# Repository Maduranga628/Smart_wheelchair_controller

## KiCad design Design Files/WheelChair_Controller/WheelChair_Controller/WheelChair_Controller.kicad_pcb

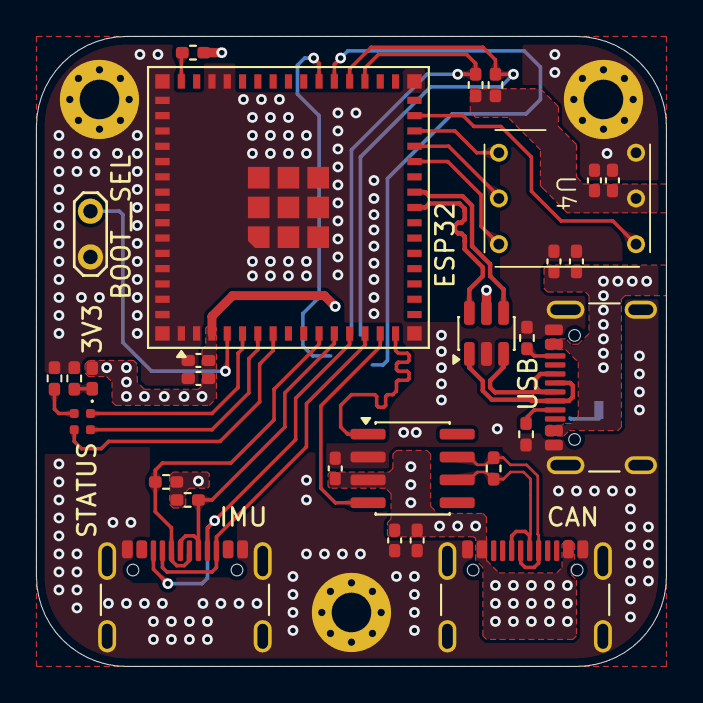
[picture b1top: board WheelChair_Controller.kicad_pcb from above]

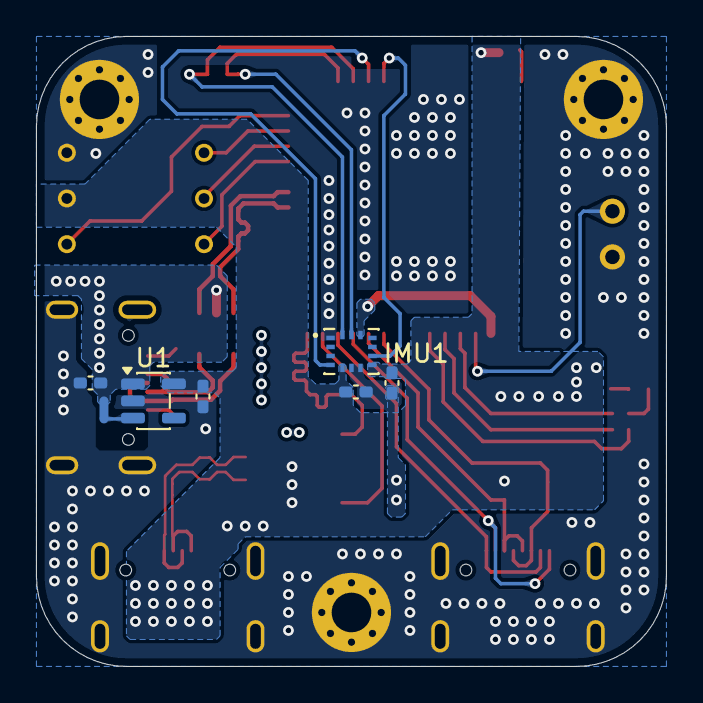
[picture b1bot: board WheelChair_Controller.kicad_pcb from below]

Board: 4 copper layers, 35.0 x 35.0 mm, 39 parts (7 on the bottom side), 33 nets.

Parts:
3V3: LED; LED_0402_1005Metric_Pad0.77x0.64mm_HandSolder
BOOT__SEL: Jumper_2_Open; TestPoint_2Pads_Pitch2.54mm_Drill0.8mm
C1, C2, C5, C6, C8, C10, C11, C12: 1u; C_0402_1005Metric_Pad0.74x0.62mm_HandSolder
C3, C4, C7, C9, C13: 100n; C_0402_1005Metric_Pad0.74x0.62mm_HandSolder
CAN: USB_C_Receptacle_USB2.0_16P; USB_C_Receptacle_GCT_USB4105-xx-A_16P_TopMnt_Horizontal
ESP32: ESP32-S3-MINI-1U; ESP32-S2-MINI-1U
IMU: USB_C_Receptacle_USB2.0_16P; USB_C_Receptacle_GCT_USB4105-xx-A_16P_TopMnt_Horizontal
IMU1: BMI270; XDCR_BMI270
MH1, MH2, MH3: MountingHole_Pad; MountingHole_2.2mm_M2_Pad_Via
NT1: NetTie_2; NetTie-2_SMD_Pad0.5mm
R1, R2: 330R; R_0402_1005Metric_Pad0.72x0.64mm_HandSolder
R3, R4, R5, R7, R8, R9, R10: 5k1; R_0402_1005Metric_Pad0.72x0.64mm_HandSolder
R6: 120R; R_0402_1005Metric_Pad0.72x0.64mm_HandSolder
STATUS: LED_RGB; LED_SK6812_EC15_1.5x1.5mm
U1: TLV75533PDBV; SOT-23-5
U2: USBLC6-2SC6; SOT-23-6
U3: SN65HVD232; SOIC-8_3.9x4.9mm_P1.27mm
U4: INMP441 Module; INMP441_Module
USB: USB_C_Receptacle_USB2.0_16P; USB_C_Receptacle_GCT_USB4105-xx-A_16P_TopMnt_Horizontal

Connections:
+3V3: 3V3.2 (A), C3.1, C4.1, C6.1, C7.1, C8.1, C9.1, C10.1, C11.1, C12.1, C13.1, CAN.A4 (VBUS), CAN.A9 (VBUS), CAN.B4 (VBUS), CAN.B9 (VBUS), ESP32.3 (3V3), IMU1.5 (VDDIO), IMU1.8 (VDD), IMU1.12 (CSB), R5.1, R7.1, R8.1, R9.1, R10.1, U1.5 (OUT), U3.3 (VCC), U4.5 (VDD)
+VBUS: C1.1, C2.1, C5.1, NT1.1, U1.1 (IN), U2.5 (VBUS), USB.A4 (VBUS), USB.A9 (VBUS), USB.B4 (VBUS), USB.B9 (VBUS)
/BOOT_SEL: BOOT__SEL.2 (B), ESP32.4 (IO0)
/CAN+: CAN.A6 (D+), CAN.B6 (D+), R6.2, U3.7 (CANH)
/CAN-: CAN.A7 (D-), CAN.B7 (D-), R6.1, U3.6 (CANL)
/CAN_RX: ESP32.14 (IO10), U3.4 (R)
/CAN_TX: ESP32.15 (IO11), U3.1 (D)
/EN: ESP32.45 (EN), R5.2
/I2S_L/R: ESP32.28 (IO33), U4.1 (L/R)
/I2S_SCL: ESP32.26 (IO26), U4.3 (SCK)
/I2S_SD: ESP32.29 (IO34), U4.4 (SD)
/I2S_WS: ESP32.27 (IO47), U4.2 (WS)
/IMU1_INT1: ESP32.35 (IO39), IMU1.4 (INT1)
/IMU1_INT2: ESP32.36 (IO40), IMU1.9 (INT2)
/IMU1_SCL: ESP32.33 (IO37), IMU1.13 (SCX), R9.2
/IMU1_SDA: ESP32.34 (IO38), IMU1.14 (SDX), R10.2
/IMU2_INT1: ESP32.13 (IO9), IMU.A5 (CC1), IMU.B5 (CC2)
/IMU2_INT2: ESP32.12 (IO8), IMU.A8 (SBU1), IMU.B8 (SBU2)
/IMU2_SCL: ESP32.10 (IO6), IMU.A7 (D-), IMU.B7 (D-), R8.2
/IMU2_SDA: ESP32.11 (IO7), IMU.A6 (D+), IMU.B6 (D+), R7.2
/LDO_EN: NT1.2, U1.3 (EN)
/PWR_RDY: 3V3.1 (K), R1.1
/STATUS: R2.2, STATUS.4 (K)
/STATUS_LED1: ESP32.6 (IO2), STATUS.2 (RA)
/STATUS_LED2: ESP32.5 (IO1), STATUS.3 (GA)
/STATUS_LED3: ESP32.7 (IO3), STATUS.1 (BA)
/USBD+: U2.3 (I/O2), USB.A6 (D+), USB.B6 (D+)
/USBD-: U2.1 (I/O1), USB.A7 (D-), USB.B7 (D-)
/USB_CC1: R4.1, USB.A5 (CC1)
/USB_CC2: R3.1, USB.B5 (CC2)
/USB_D+: ESP32.24 (USB_D+), U2.4 (I/O2)
/USB_D-: ESP32.23 (USB_D-), U2.6 (I/O1)
GND: BOOT__SEL.1 (A), C1.2, C2.2, C3.2, C4.2, C5.2, C6.2, C7.2, C8.2, C9.2, C10.2, C11.2, C12.2, C13.2, CAN.A1 (GND), CAN.A12 (GND), CAN.B1 (GND), CAN.B12 (GND), CAN.S1 (SHIELD), ESP32.1 (GND), ESP32.2 (GND), ESP32.42 (GND), ESP32.43 (GND), ESP32.46 (GND), ESP32.47 (GND), ESP32.48 (GND), ESP32.49 (GND), ESP32.50 (GND), ESP32.51 (GND), ESP32.52 (GND), ESP32.53 (GND), ESP32.54 (GND), ESP32.55 (GND), ESP32.56 (GND), ESP32.57 (GND), ESP32.58 (GND), ESP32.59 (GND), ESP32.60 (GND), ESP32.61 (GND), ESP32.62 (GND), ESP32.63 (GND), ESP32.64 (GND), ESP32.65 (GND), IMU.A1 (GND), IMU.A12 (GND), IMU.B1 (GND), IMU.B12 (GND), IMU.S1 (SHIELD), IMU1.1 (SDO), IMU1.6 (GNDIO), IMU1.7 (GND), MH1.1, MH2.1, MH3.1, R1.2, R2.1, R3.2, R4.2, U1.2 (GND), U2.2 (GND), U3.2 (GND), U4.6 (GND), USB.A1 (GND), USB.A12 (GND), USB.B1 (GND), USB.B12 (GND), USB.S1 (SHIELD)

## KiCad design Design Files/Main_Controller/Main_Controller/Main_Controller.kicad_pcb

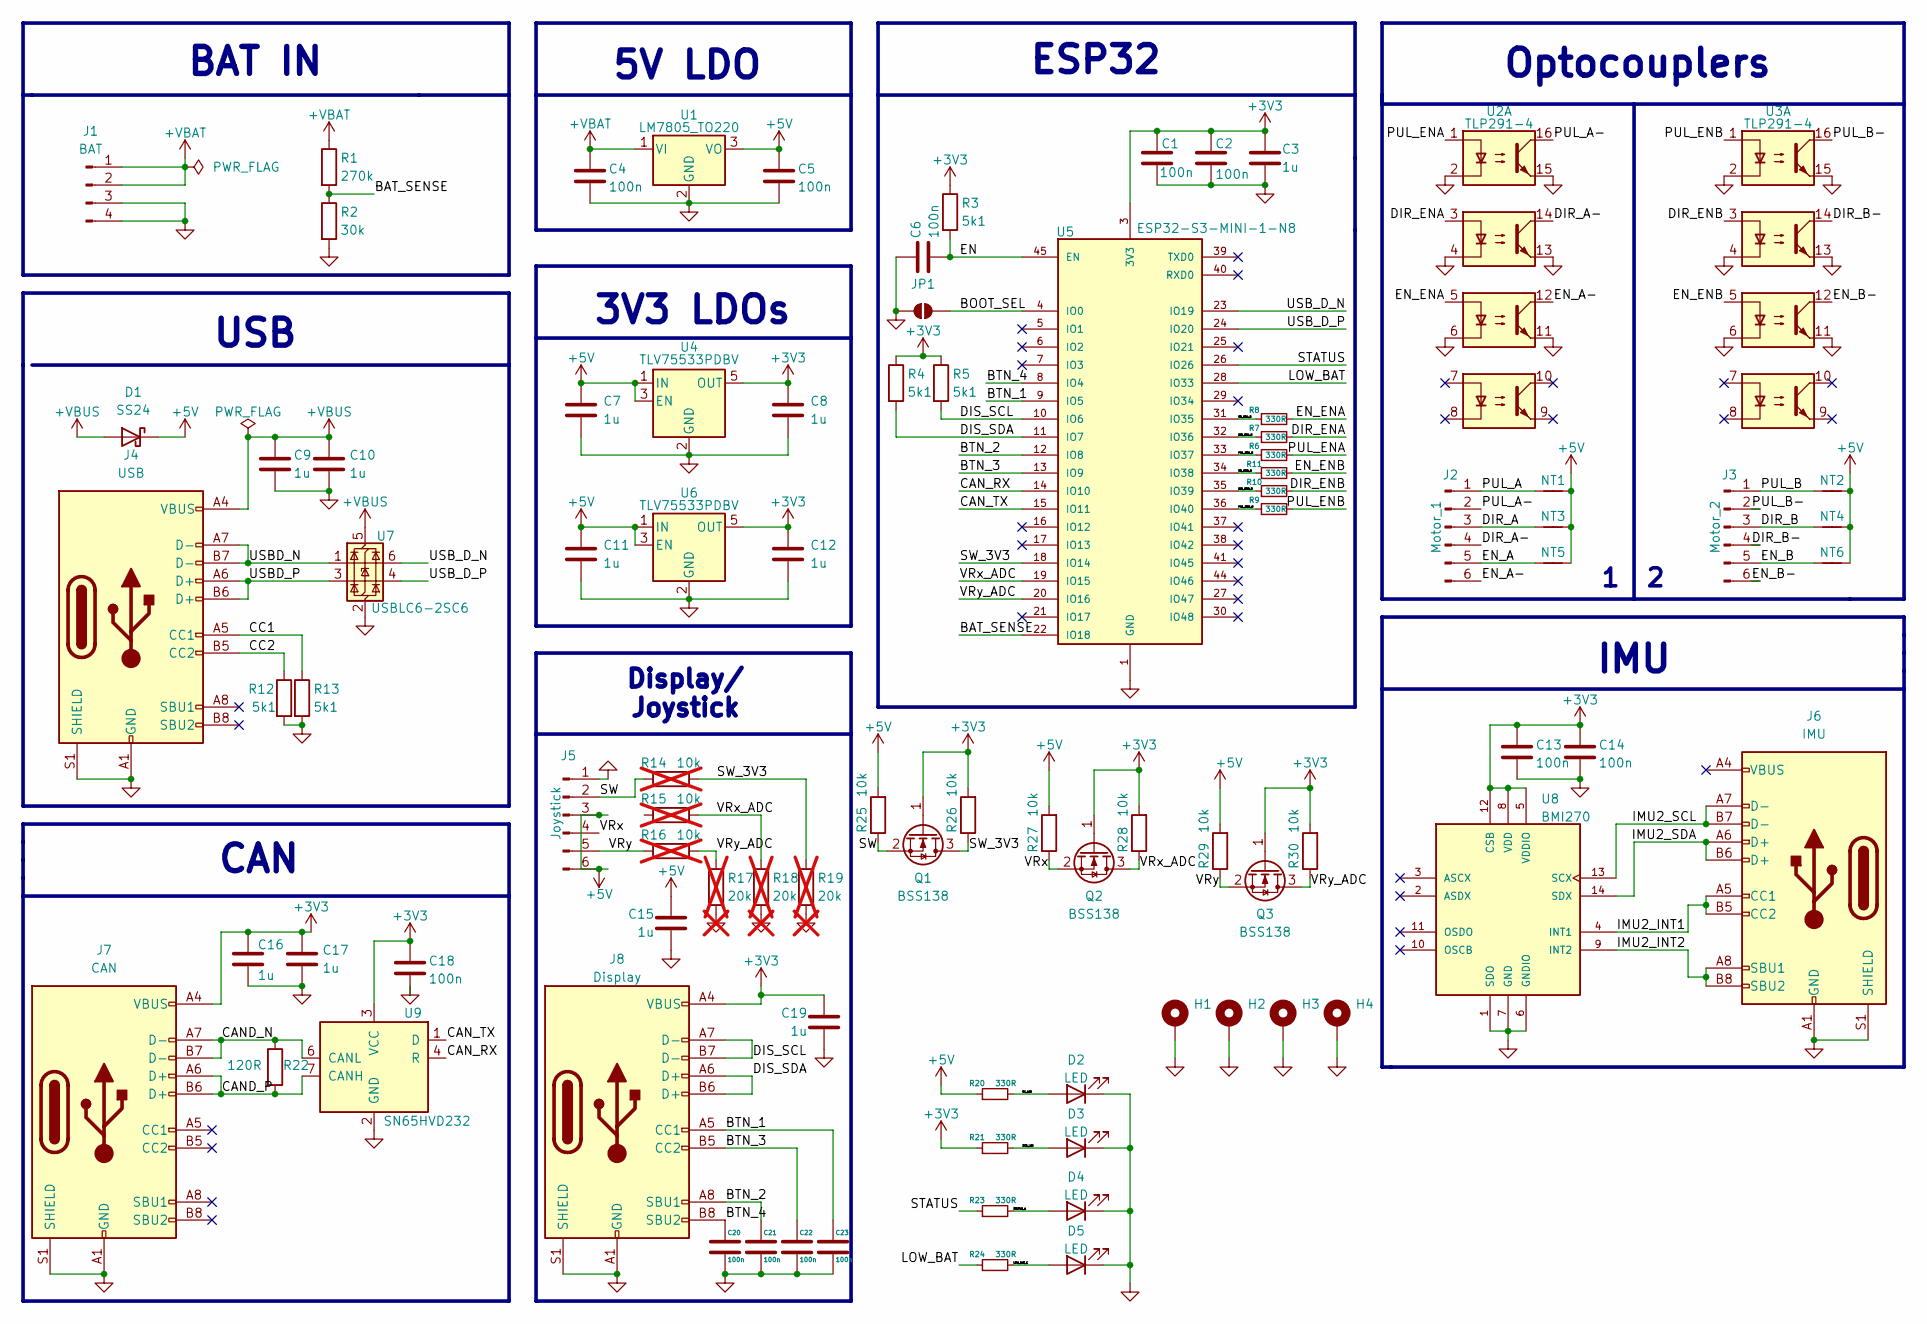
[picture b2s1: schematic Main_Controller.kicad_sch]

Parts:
C1, C2, C4, C5, C6, C13, C14, C18, C20, C21, C22, C23: 100n; C_0603_1608Metric
C3, C7, C8, C9, C10, C11, C12, C15, C16, C17, C19: 1u; C_0603_1608Metric
D1: SS24; D_SMA
D2, D3, D4, D5: LED; LED_0603_1608Metric
H1, H2, H3, H4: MountingHole_Pad_MP; MountingHole_3.2mm_M3_Pad_Via
J1: BAT; Molex_KK-254_AE-6410-04A_1x04_P2.54mm_Vertical
J2: Motor_1; PinSocket_1x06_P2.54mm_Vertical
J3: Motor_2; PinSocket_1x06_P2.54mm_Vertical
J4: USB; USB_C_Receptacle_GCT_USB4105-xx-A_16P_TopMnt_Horizontal
J5: Joystick; PinSocket_1x06_P2.54mm_Vertical
J6: IMU; USB_C_Receptacle_GCT_USB4105-xx-A_16P_TopMnt_Horizontal
J7: CAN; USB_C_Receptacle_GCT_USB4105-xx-A_16P_TopMnt_Horizontal
J8: Display; USB_C_Receptacle_GCT_USB4105-xx-A_16P_TopMnt_Horizontal
JP1: SolderJumper_2_Open; SolderJumper-2_P1.3mm_Open_RoundedPad1.0x1.5mm
NT1, NT2, NT3, NT4, NT5, NT6: NetTie_2; NetTie-2_SMD_Pad0.5mm
Q1, Q2, Q3: BSS138; SOT-23
R1: 270k; R_0603_1608Metric; Manufacturer Part No. RC0603FR-07270KL; LCSC No. C137755
R2: 30k; R_0603_1608Metric; Manufacturer Part No. RC0603FR-0730KL; LCSC No. C100001
R3, R4, R5, R12, R13: 5k1; R_0603_1608Metric
R6, R7, R8, R9, R10, R11, R20, R21, R23, R24: 330R; R_0603_1608Metric; Manufacturer Part No. RC0603FR-07330RL; LCSC No. C105881
R14, R15, R16: 10k; R_0603_1608Metric; Manufacturer Part No. RC0603FR-0710KL; LCSC No. C98220; not fitted
R17, R18, R19: 20k; R_0603_1608Metric; Manufacturer Part No. RC0603FR-0720KL; LCSC No. C105575; not fitted
R22: 120R; R_0603_1608Metric
R25, R26, R27, R28, R29, R30: 10k; R_0603_1608Metric; Manufacturer Part No. RC0603FR-0710KL; LCSC No. C98220
U1: LM7805_TO220; SOT-223-3_TabPin2; Manufacturer Part No. LM7805MPX/NOPB; LCSC No. C2848241
U2: TLP291-4; SOIC-16_4.55x10.3mm_P1.27mm; Manufacturer Part No. TLP291-4(TP,E); LCSC No. C516180
U3: TLP291-4; SOIC-16_4.55x10.3mm_P1.27mm
U4, U6: TLV75533PDBV; SOT-23-5
U5: ESP32-S3-MINI-1-N8; PARTREV v0.6
U7: USBLC6-2SC6; SOT-23-6
U8: BMI270
U9: SN65HVD232; SOIC-8_3.9x4.9mm_P1.27mm

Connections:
+3V3: C1.1, C2.1, C3.1, C8.1, C12.1, C13.1, C14.1, C16.1, C17.1, C18.1, C19.1, J7.A4 (VBUS), J7.A9 (VBUS), J7.B4 (VBUS), J7.B9 (VBUS), J8.A4 (VBUS), J8.A9 (VBUS), J8.B4 (VBUS), J8.B9 (VBUS), Q1.1 (G), Q2.1 (G), Q3.1 (G), R3.1, R4.1, R5.1, R21.1, R26.2, R28.2, R30.2, U4.5 (OUT), U5.3 (3V3), U6.5 (OUT), U8.5 (VDDIO), U8.8 (VDD), U8.12 (CSB), U9.3 (VCC)
+5V: C5.1, C7.1, C11.1, C15.1, D1.1 (K), J5.3, J5.6, NT1.2, NT2.2, NT3.2, NT4.2, NT5.2, NT6.2, R20.1, R25.2, R27.2, R29.2, U1.3 (VO), U4.1 (IN), U4.3 (EN), U6.1 (IN), U6.3 (EN)
+VBAT: C4.1, J1.1, J1.2, R1.1, U1.1 (VI)
+VBUS: C9.1, C10.1, D1.2 (A), J4.A4 (VBUS), J4.A9 (VBUS), J4.B4 (VBUS), J4.B9 (VBUS), U7.5 (VBUS)
/3V3_LED: D3.2 (A), R21.2
/5V_LED: D2.2 (A), R20.2
/BAT_SENSE: R1.2, R2.1, U5.22 (IO18)
/BOOT_SEL: JP1.2 (B), U5.4 (IO0)
/BTN_1: C23.1, J8.A5 (CC1), U5.9 (IO5)
/BTN_2: C21.1, J8.A8 (SBU1), U5.12 (IO8)
/BTN_3: C22.1, J8.B5 (CC2), U5.13 (IO9)
/BTN_4: C20.1, J8.B8 (SBU2), U5.8 (IO4)
/CAND_N: J7.A7 (D-), J7.B7 (D-), R22.1, U9.6 (CANL)
/CAND_P: J7.A6 (D+), J7.B6 (D+), R22.2, U9.7 (CANH)
/CAN_RX: U5.14 (IO10), U9.4 (R)
/CAN_TX: U5.15 (IO11), U9.1 (D)
/CC1: J4.A5 (CC1), R13.1
/CC2: J4.B5 (CC2), R12.1
/DIR_A: J2.3, NT3.1
/DIR_A-: J2.4, U2.14
/DIR_B: J3.3, NT4.1
/DIR_B-: J3.4, U3.14
/DIR_ENA: R7.2, U2.3
/DIR_ENA_R: R7.1, U5.32 (IO36)
/DIR_ENB: R10.2, U3.3
/DIR_ENB_R: R10.1, U5.35 (IO39)
/DIS_SCL: J8.A7 (D-), J8.B7 (D-), R5.2, U5.10 (IO6)
/DIS_SDA: J8.A6 (D+), J8.B6 (D+), R4.2, U5.11 (IO7)
/EN: C6.2, R3.2, U5.45 (EN)
/EN_A: J2.5, NT5.1
/EN_A-: J2.6, U2.12
/EN_B: J3.5, NT6.1
/EN_B-: J3.6, U3.12
/EN_ENA: R8.2, U2.5
/EN_ENA_R: R8.1, U5.31 (IO35)
/EN_ENB: R11.2, U3.5
/EN_ENB_R: R11.1, U5.34 (IO38)
/IMU2_INT1: J6.A5 (CC1), J6.B5 (CC2), U8.4 (INT1)
/IMU2_INT2: J6.A8 (SBU1), J6.B8 (SBU2), U8.9 (INT2)
/IMU2_SCL: J6.A7 (D-), J6.B7 (D-), U8.13 (SCX)
/IMU2_SDA: J6.A6 (D+), J6.B6 (D+), U8.14 (SDX)
/LOW_BAT: R24.1, U5.28 (IO33)
/LOW_BAT_C: D5.2 (A), R24.2
/PUL_A: J2.1, NT1.1
/PUL_A-: J2.2, U2.16
/PUL_B: J3.1, NT2.1
/PUL_B-: J3.2, U3.16
/PUL_ENA: R6.2, U2.1
/PUL_ENA_R: R6.1, U5.33 (IO37)
/PUL_ENB: R9.2, U3.1
/PUL_ENB_R: R9.1, U5.36 (IO40)
/STATUS: R23.1, U5.26 (IO26)
/STATUS_A: D4.2 (A), R23.2
/SW: J5.2, Q1.2 (S), R14.1, R25.1
/SW_3V3: Q1.3 (D), R14.2, R19.1, R26.1, U5.18 (IO14)
/USBD_N: J4.A7 (D-), J4.B7 (D-), U7.1 (I/O1)
/USBD_P: J4.A6 (D+), J4.B6 (D+), U7.3 (I/O2)
/USB_D_N: U5.23 (IO19), U7.6 (I/O1)
/USB_D_P: U5.24 (IO20), U7.4 (I/O2)
/VRx: J5.4, Q2.2 (S), R27.1
/VRx_ADC: Q2.3 (D), R15.2, R18.1, R28.1, U5.19 (IO15)
/VRy: J5.5, Q3.2 (S), R16.1, R29.1
/VRy_ADC: Q3.3 (D), R16.2, R17.1, R30.1, U5.20 (IO16)
GND: C1.2, C2.2, C3.2, C4.2, C5.2, C6.1, C7.2, C8.2, C9.2, C10.2, C11.2, C12.2, C13.2, C14.2, C15.2, C16.2, C17.2, C18.2, C19.2, C20.2, C21.2, C22.2, C23.2, D2.1 (K), D3.1 (K), D4.1 (K), D5.1 (K), H1.MP, H2.MP, H3.MP, H4.MP, J1.3, J1.4, J4.A1 (GND), J4.A12 (GND), J4.B1 (GND), J4.B12 (GND), J4.S1 (SHIELD), J5.1, J6.A1 (GND), J6.A12 (GND), J6.B1 (GND), J6.B12 (GND), J6.S1 (SHIELD), J7.A1 (GND), J7.A12 (GND), J7.B1 (GND), J7.B12 (GND), J7.S1 (SHIELD), J8.A1 (GND), J8.A12 (GND), J8.B1 (GND), J8.B12 (GND), J8.S1 (SHIELD), JP1.1 (A), R2.2, R12.2, R13.2, R17.2, R18.2, R19.2, U1.2 (GND), U2.2, U2.4, U2.6, U2.11, U2.13, U2.15, U3.2, U3.4, U3.6, U3.11, U3.13, U3.15, U4.2 (GND), U5.1 (GND), U5.2 (GND__1), U5.42 (GND__2), U5.43 (GND__3), U5.46 (GND__4), U5.47 (GND__5), U5.48 (GND__6), U5.49 (GND__7), U5.50 (GND__8), U5.51 (GND__9), U5.52 (GND__10), U5.53 (GND__11), U5.54 (GND__12), U5.55 (GND__13), U5.56 (GND__14), U5.57 (GND__15), U5.58 (GND__16), U5.59 (GND__17), U5.60 (GND__18), U5.61 (GND__19), U5.61_1 (GND__20), U5.61_2 (GND__21), U5.61_3 (GND__22), U5.61_4 (GND__23), U5.61_5 (GND__24), U5.61_6 (GND__25), U5.61_7 (GND__26), U5.61_8 (GND__27), U5.62 (GND__28), U5.63 (GND__29), U5.64 (GND__30), U5.65 (GND__31), U6.2 (GND), U7.2 (GND), U8.1 (SDO), U8.6 (GNDIO), U8.7 (GND), U9.2 (GND)

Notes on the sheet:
Display/ Joystick
5V LDO
BAT IN
ESP32
Optocouplers
IMU
CAN
3V3 LDOs
USB

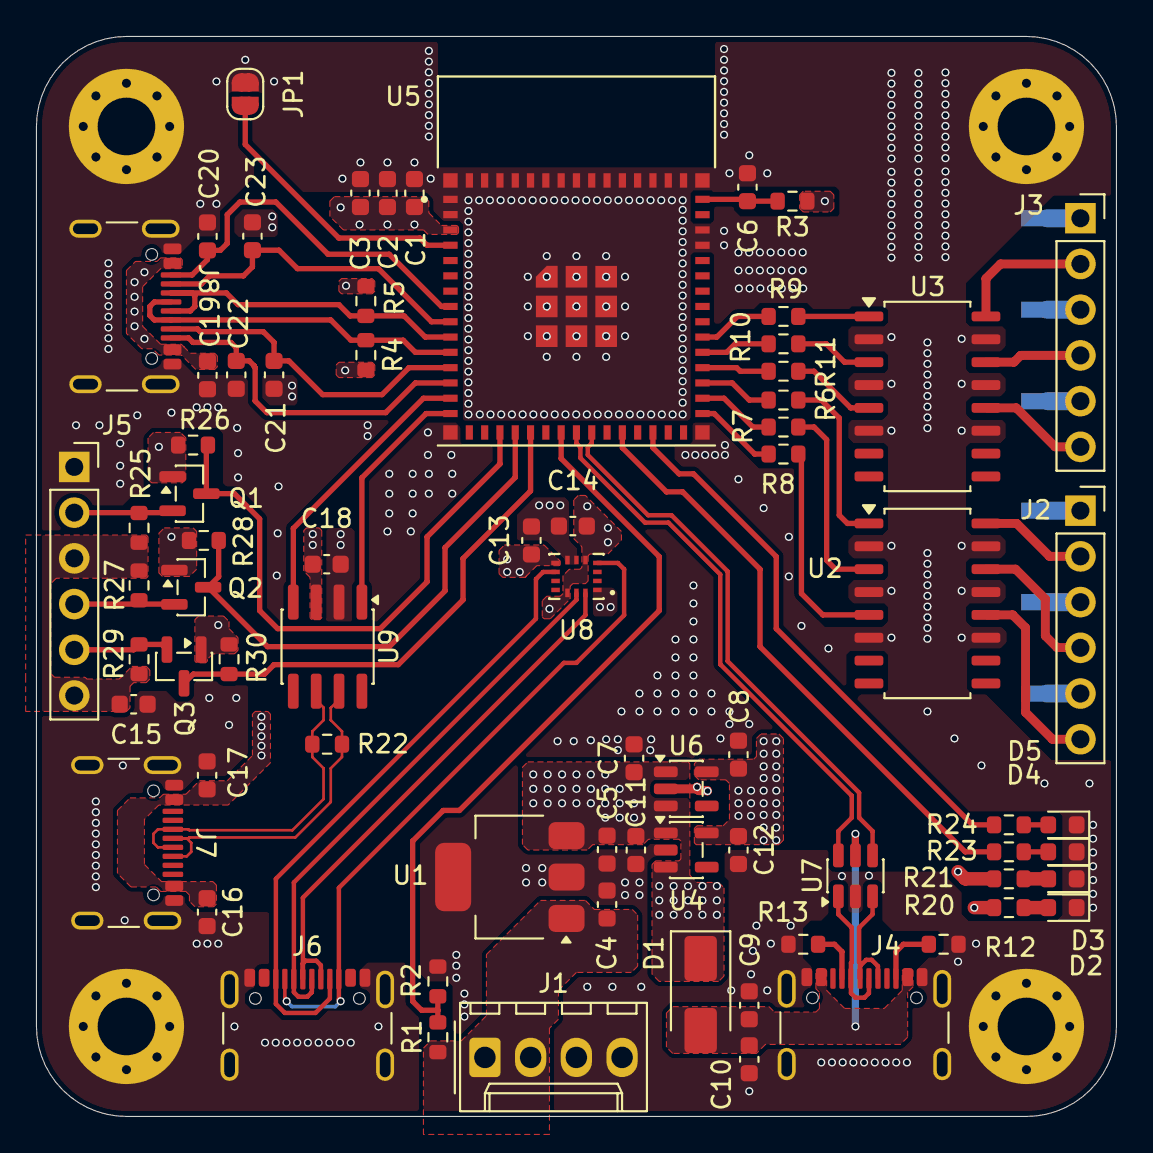
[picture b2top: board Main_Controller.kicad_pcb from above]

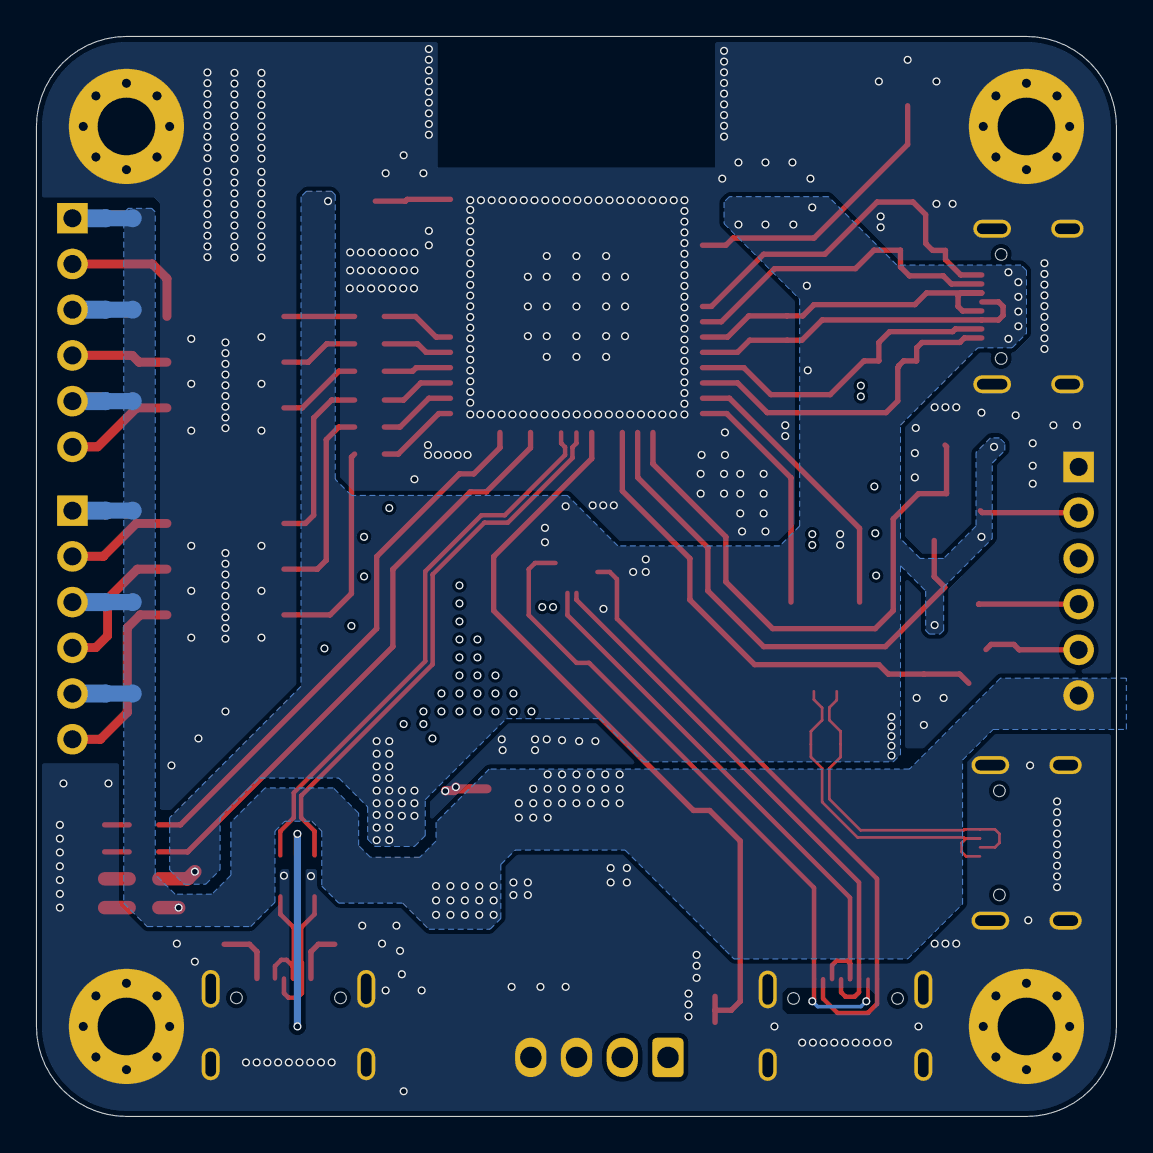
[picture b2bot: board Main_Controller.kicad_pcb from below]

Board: 4 copper layers, 60.0 x 60.0 mm, 83 parts (6 on the bottom side), 64 nets.

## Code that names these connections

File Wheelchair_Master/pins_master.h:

#pragma once

// =====================
// OLED SSD1306 (I2C)
// =====================
static const int PIN_OLED_SDA = 7;
static const int PIN_OLED_SCL = 6;

// =====================
// Buttons (GPIO + INPUT_PULLUP)
// =====================
// BUTTON1 = UP
static const int PIN_BTN_UP    = 2;
// BUTTON2 = DOWN
static const int PIN_BTN_DOWN  = 4;
// BUTTON3 = ENTER
static const int PIN_BTN_ENTER = 12;
// BUTTON4 = BACK
static const int PIN_BTN_BACK  = 13;

// =====================
// Joystick (Analog)
// =====================
// Joystick switch pin (IO14) was marked "Do Not Use" in your pinout
static const int PIN_JOY_X = 15;
static const int PIN_JOY_Y = 16;

// =====================
// Battery sensing (ADC)
// =====================
static const int PIN_BAT_SENSE = 18;

// =====================
// CAN (TWAI)
// =====================
// Your sheet showed CAN RX = IO10 and CAN TX = IO11 on the bus side.
// Master needs both for TWAI.
static const int PIN_CAN_RX = 10;
static const int PIN_CAN_TX = 11;

// =====================
// Stepper Driver 1 (Motor 1)
// EN/DIR/PUL signals
// =====================
// LEFT motor = M1
static const int PIN_M1_EN  = 45;
static const int PIN_M1_DIR = 42;
static const int PIN_M1_PUL = 1;


// =====================
// Stepper Driver 2 (Motor 2)
// EN/DIR/PUL signals
// =====================

// RIGHT motor = M2
static const int PIN_M2_EN  = 48;
static const int PIN_M2_DIR = 38;
static const int PIN_M2_PUL = 39;

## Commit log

2026-03-18 Create a
